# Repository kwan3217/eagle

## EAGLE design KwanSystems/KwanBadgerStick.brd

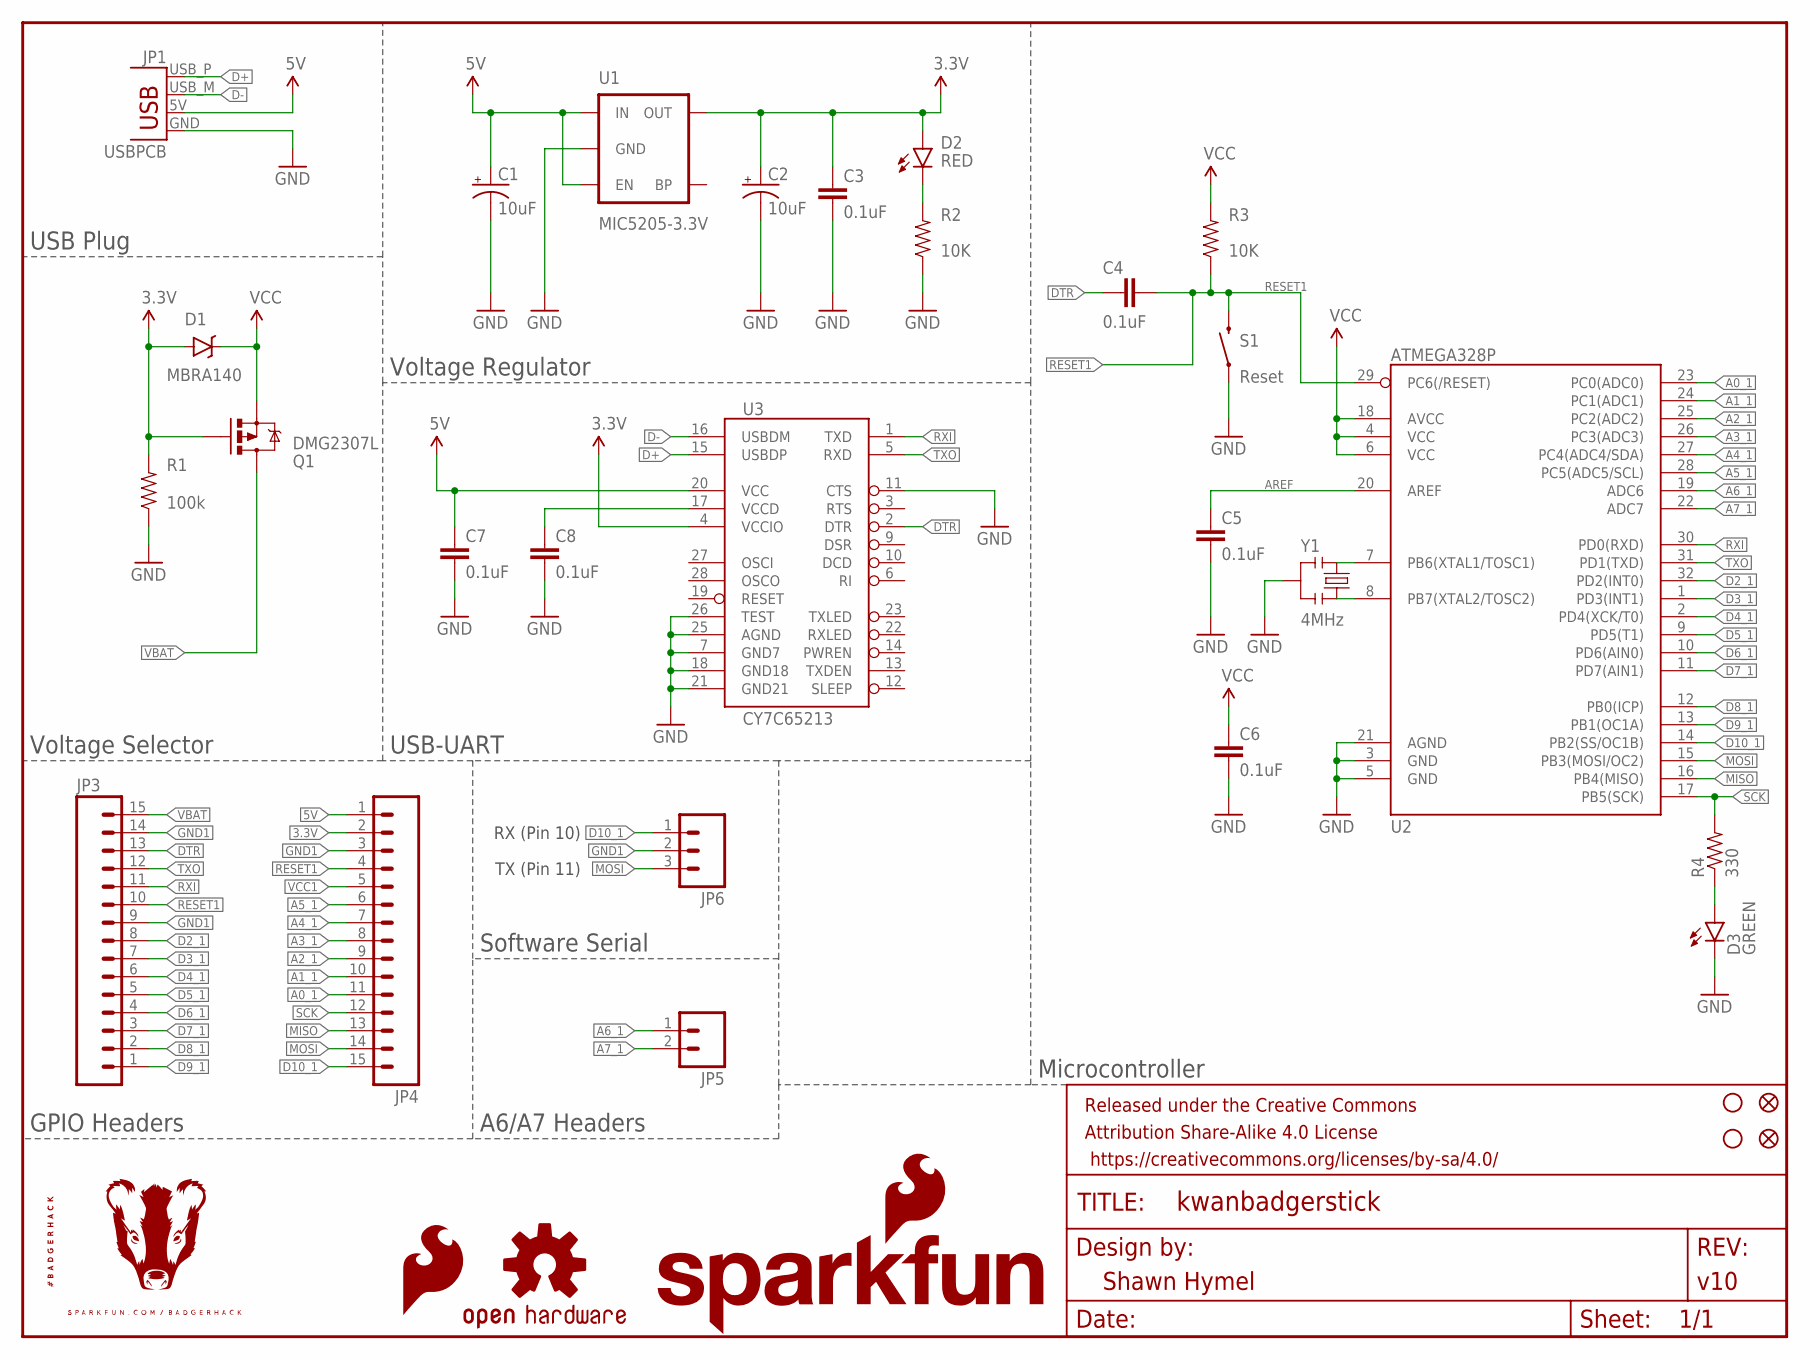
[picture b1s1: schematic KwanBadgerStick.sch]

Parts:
C1, C2: 10uF; EIA3216
C3, C4, C5, C6, C7, C8: 0.1uF; 0603-CAP
D1: MBRA140; SMA-DIODE
D2: RED; LED-0603
D3: GREEN; LED-0603
FID1, FID2: FIDUCIAL1X2; FIDUCIAL-1X2
FRAME1: FRAME-LETTER; CREATIVE_COMMONS
JP1: USBPCB; USB-A-PCB
JP3, JP4: M15LOCK_NO_SILK; 1X15_LOCK_NO_SILK
JP5: M021X02_NO_SILK; 1X02_NO_SILK
JP6: M03LOCK Female; 1X03_LOCK_NO_SILK
LOGO1: SFE_LOGO_FLAME.1_INCH; SFE_LOGO_FLAME_.1
LOGO2: OSHW-LOGOS; OSHW-LOGO-S
Q1: DMG2307L; SOT23-3
R1: 100k; 0603-RES
R2, R3: 10K; 0603-RES
R4: 330; 0603-RES
S1: SWITCH-MOMENTARY-2SMD-REDUNDANT; TACTILE-SWITCH-SMD
STANDOFF1, STANDOFF2: STAND-OFF
U1: MIC5205-3.3V; SOT23-5
U2: ATMEGA328P; TQFP32-08
U3: CY7C65213; SSOP28DB
U$1: SFE_LOGO_NAME_FLAME.1_INCH; SFE_LOGO_NAME_FLAME_.1
U$2: BADGERHACK_LOGODUMMY; DUMMY
Y1: 4MHz; RESONATOR-SMD_MED

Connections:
3.3V: C2.A (+), C3.1, D1.A, D2.A, JP4.2, Q1.1 (G), R1.2, U1.5 (OUT), U3.4 (VCCIO)
5V: C1.A (+), C7.1, JP1.5V (VBUS), JP4.1, U1.1 (IN), U1.3 (EN), U3.20 (VCC)
A0_1: JP4.11, U2.23 (PC0(ADC0))
A1_1: JP4.10, U2.24 (PC1(ADC1))
A2_1: JP4.9, U2.25 (PC2(ADC2))
A3_1: JP4.8, U2.26 (PC3(ADC3))
A4_1: JP4.7, U2.27 (PC4(ADC4/SDA))
A5_1: JP4.6, U2.28 (PC5(ADC5/SCL))
A6_1: JP5.1, U2.19 (ADC6)
A7_1: JP5.2, U2.22 (ADC7)
AREF: C5.1, U2.20 (AREF)
D2_1: JP3.8, U2.32 (PD2(INT0))
D3_1: JP3.7, U2.1 (PD3(INT1))
D4_1: JP3.6, U2.2 (PD4(XCK/T0))
D5_1: JP3.5, U2.9 (PD5(T1))
D6_1: JP3.4, U2.10 (PD6(AIN0))
D7_1: JP3.3, U2.11 (PD7(AIN1))
D8_1: JP3.2, U2.12 (PB0(ICP))
D9_1: JP3.1, U2.13 (PB1(OC1A))
D10_1: JP4.15, JP6.1, U2.14 (PB2(SS/OC1B))
D+: JP1.USB_P (D+), U3.15 (USBDP)
D-: JP1.USB_M (D-), U3.16 (USBDM)
DTR: C4.1, JP3.13, U3.2 (DTR)
GND1: C1.C (-), C2.C (-), C3.2, C5.2, C6.2, C7.2, C8.2, D3.C, JP1.GND, JP3.9, JP3.14, JP4.3, JP6.2, R1.1, R2.1, S1.1, S1.2 (1), U1.2 (GND), U2.3 (GND), U2.5 (GND), U2.21 (AGND), U3.7 (GND7), U3.11 (CTS), U3.18 (GND18), U3.21 (GND21), U3.25 (AGND), U3.26 (TEST), Y1.2
MISO: JP4.13, U2.16 (PB4(MISO))
MOSI: JP4.14, JP6.3, U2.15 (PB3(MOSI/OC2))
unnamed: D3.A, R4.1
unnamed: C8.1, U3.17 (VCCD)
unnamed: D2.C, R2.2
unnamed: U2.7 (PB6(XTAL1/TOSC1)), Y1.1
unnamed: U2.8 (PB7(XTAL2/TOSC2)), Y1.3
RESET1: C4.2, JP3.10, JP4.4, R3.1, S1.3 (2), S1.4 (2), U2.29 (PC6(/RESET))
RXI: JP3.11, U2.30 (PD0(RXD)), U3.1 (TXD)
SCK: JP4.12, R4.2, U2.17 (PB5(SCK))
TXO: JP3.12, U2.31 (PD1(TXD)), U3.5 (RXD)
VBAT: JP3.15, Q1.3 (D)
VCC1: C6.1, D1.C, JP4.5, Q1.2 (S), R3.2, U2.4 (VCC), U2.6 (VCC), U2.18 (AVCC)

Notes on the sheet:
RX (Pin 10)
TX (Pin 11)
USB Plug
Voltage Selector
GPIO Headers
A6/A7 Headers
Software Serial
USB-UART
Voltage Regulator
Microcontroller

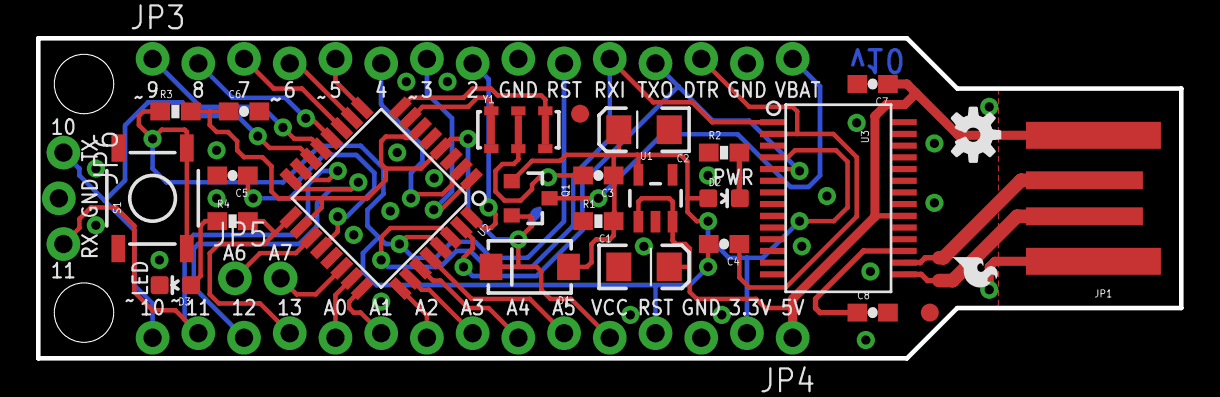
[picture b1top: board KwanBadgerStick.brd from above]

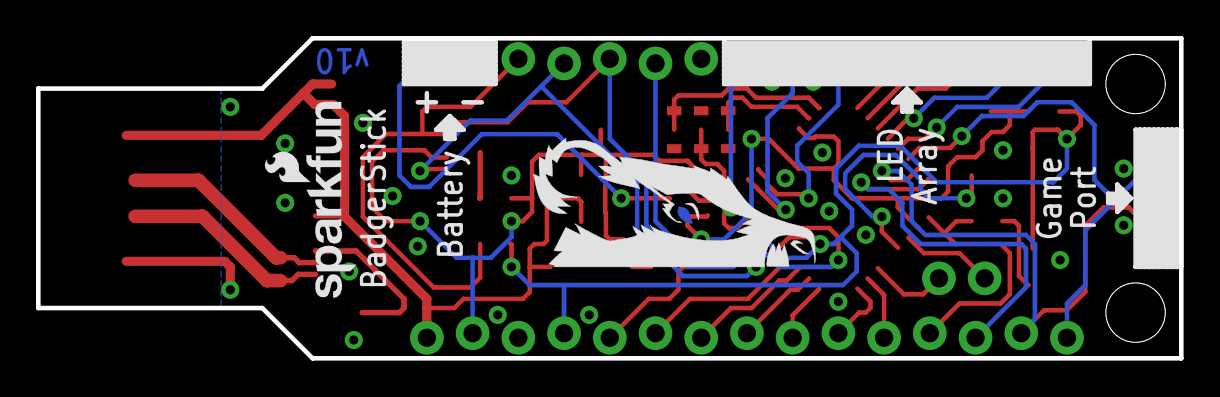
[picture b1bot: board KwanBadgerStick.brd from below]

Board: 2 copper layers, 63.5 x 17.8 mm, 36 parts (2 on the bottom side), 37 nets.

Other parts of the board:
U$3: HALF_BADGER

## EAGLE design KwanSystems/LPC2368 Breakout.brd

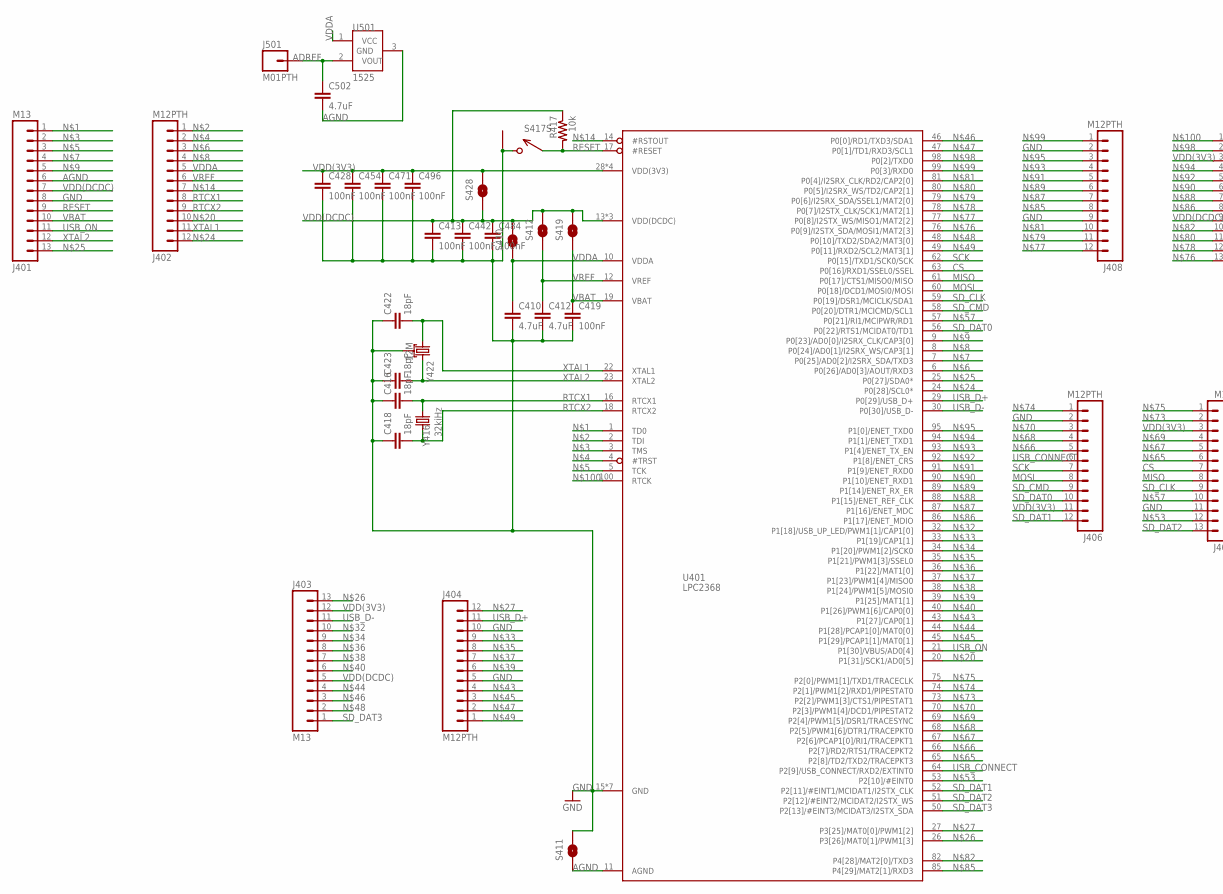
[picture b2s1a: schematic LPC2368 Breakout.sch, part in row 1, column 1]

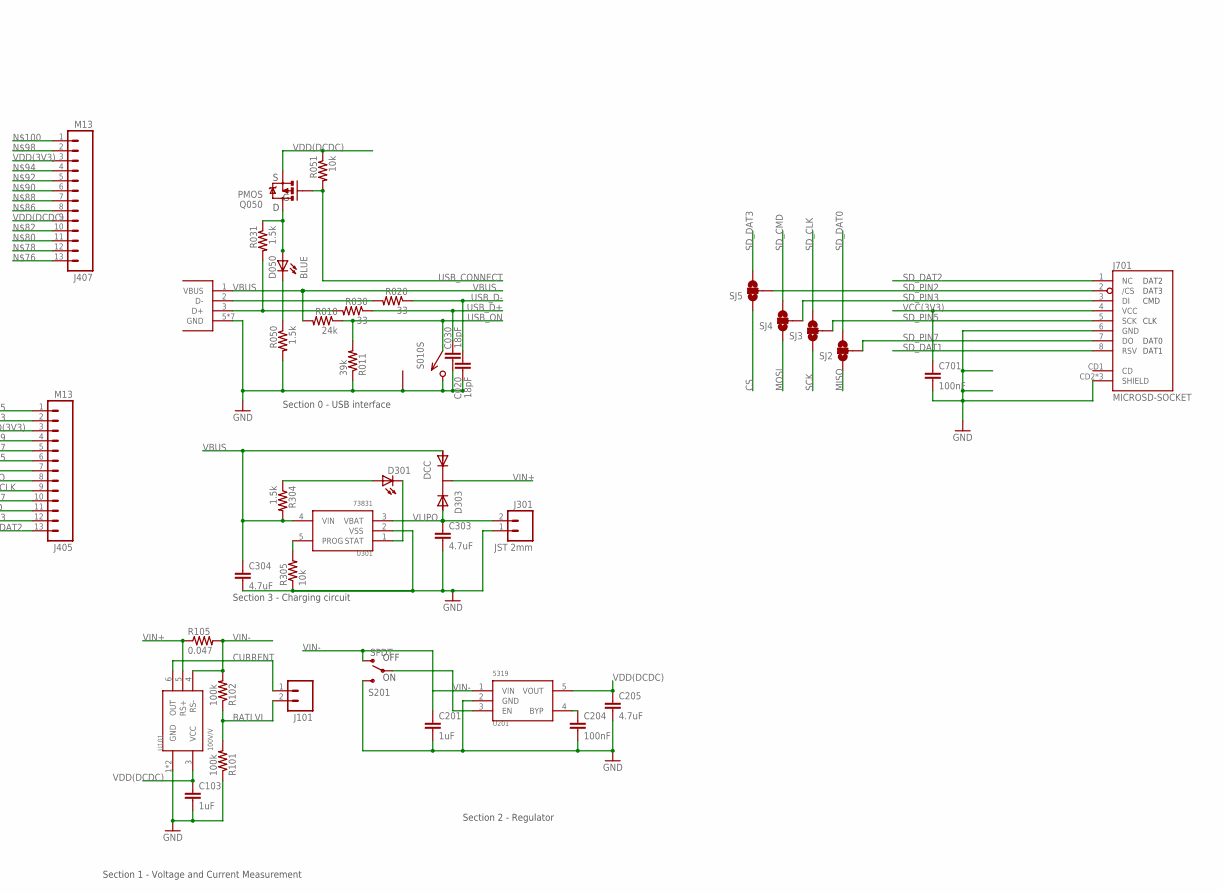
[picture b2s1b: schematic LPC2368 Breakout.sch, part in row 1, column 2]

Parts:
C020, C030, C416, C418, C422, C423: 18pF; 0402-CAP
C103, C201: 1uF; 0402-CAP
C204, C413, C419, C428, C442, C454, C471, C484, C496, C701: 100nF; 0402-CAP
C205, C303, C304, C410, C412, C502: 4.7uF; 0402-CAP
D050: BLUE; LED-0603
D301: YELLOW; LED-0603
D303: DCC; SOT-23-3
J001: USB_MICROB_JST; UB-MC5BR3-SD204-4S
J101: M02PTH; 1X02
J301: JST 2mm; JST-2-SMD
J401, J403, J405, J407: M13; 1X13
J402, J404, J406, J408: M12PTH; 1X12
J501: M01PTH; 1X01
J701: MICROSD-SOCKET; MICROSD-SOCKET-PP
Q050: PMOS; SOT23-3
R010: 24k; 0402-RES
R011: 39k; 0402-RES
R020, R030: 33; 0402-RES
R031, R050, R304: 1.5k; 0402-RES
R051, R305, R417: 10k; 0402-RES
R101, R102: 100k; 0402-RES
R105: 0.047; 0402-RES
S010, S417: SPST; B3U-1100P
S201: SPDT; AYZ0202
S410, S411, S412, S419, S428: SOLDERJUMPERNO; SJ_2S-NO
SJ2, SJ3, SJ4, SJ5: SOLDERJUMPER_2WAYS; SJ_3
U101: 100V/V; SOT-23-6
U201: 5319; SOT-23-5
U301: 73831; SOT-23-5
U401: LPC2368; LQFP100
U501: 1525; SOT-23-3
Y416: 32kiHz; CRYSTAL-32KHZ-SMD
Y422: 12M; CRYSTAL_SMD

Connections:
ADREF: C502.1, J501.1, U501.2 (VOUT)
AGND: C502.2, J401.6, S411.1, U401.11 (AGND), U501.3 (GND)
BATLVL: J101.2, R101.2, R102.1
CONN_D+: J001.3 (D+), R030.2, R031.2
CONN_D-: J001.2 (D-), R020.2
CS: J405.7, SJ5.1, U401.63 (P0[16]/RXD1/SSEL0/SSEL)
CURRENT: J101.1, U101.6 (OUT)
C_STAT: D301.C, U301.1 (STAT)
DR_STAT: D301.A, R304.1
MISO: J405.8, SJ2.1, U401.61 (P0[17]/CTS1/MISO0/MISO)
MOSI: J406.8, SJ4.1, U401.60 (P0[18]/DCD1/MOSI0/MOSI)
unnamed: J401.1, U401.1 (TD0)
unnamed: J402.1, U401.2 (TDI)
unnamed: J401.2, U401.3 (TMS)
unnamed: J402.2, U401.4 (#TRST)
unnamed: J401.3, U401.5 (TCK)
unnamed: J402.3, U401.6 (P0[26]/AD0[3]/AOUT/RXD3)
unnamed: J401.4, U401.7 (P0[25]/AD0[2]/I2SRX_SDA/TXD3)
unnamed: J402.4, U401.8 (P0[24]/AD0[1]/I2SRX_WS/CAP3[1])
unnamed: J401.5, U401.9 (P0[23]/AD0[0]/I2SRX_CLK/CAP3[0])
unnamed: R305.2, U301.5 (PROG)
unnamed: J402.7, U401.14 (#RSTOUT)
unnamed: C204.1, U201.4 (BYP)
unnamed: D050.C, R050.1
unnamed: S201.2, U201.3 (EN)
unnamed: J402.10, U401.20 (P1[31]/SCK1/AD0[5])
unnamed: J402.12, U401.24 (P0[28]/SCL0*)
unnamed: J401.13, U401.25 (P0[27]/SDA0*)
unnamed: J403.13, U401.26 (P3[26]/MAT0[1]/PWM1[3])
unnamed: J404.12, U401.27 (P3[25]/MAT0[0]/PWM1[2])
unnamed: D050.A, Q050.3 (D), R031.1
unnamed: J403.10, U401.32 (P1[18]/USB_UP_LED/PWM1[1]/CAP1[0])
unnamed: J404.9, U401.33 (P1[19]/CAP1[1])
unnamed: J403.9, U401.34 (P1[20]/PWM1[2]/SCK0)
unnamed: J404.8, U401.35 (P1[21]/PWM1[3]/SSEL0)
unnamed: J403.8, U401.36 (P1[22]/MAT1[0])
unnamed: J404.7, U401.37 (P1[23]/PWM1[4]/MISO0)
unnamed: J403.7, U401.38 (P1[24]/PWM1[5]/MOSI0)
unnamed: J404.6, U401.39 (P1[25]/MAT1[1])
unnamed: J403.6, U401.40 (P1[26]/PWM1[6]/CAP0[0])
unnamed: J404.4, U401.43 (P1[27]/CAP0[1])
unnamed: J403.4, U401.44 (P1[28]/PCAP1[0]/MAT0[0])
unnamed: J404.3, U401.45 (P1[29]/PCAP1[1]/MAT0[1])
unnamed: J403.3, U401.46 (P0[0]/RD1/TXD3/SDA1)
unnamed: J404.2, U401.47 (P0[1]/TD1/RXD3/SCL1)
unnamed: J403.2, U401.48 (P0[10]/TXD2/SDA2/MAT3[0])
unnamed: J404.1, U401.49 (P0[11]/RXD2/SCL2/MAT3[1])
unnamed: J405.12, U401.53 (P2[10]/#EINT0)
unnamed: J405.10, U401.57 (P0[21]/RI1/MCIPWR/RD1)
unnamed: J405.6, U401.65 (P2[8]/TD2/TXD2/TRACEPKT3)
unnamed: J406.5, U401.66 (P2[7]/RD2/RTS1/TRACEPKT2)
unnamed: J405.5, U401.67 (P2[6]/PCAP1[0]/RI1/TRACEPKT1)
unnamed: J406.4, U401.68 (P2[5]/PWM1[6]/DTR1/TRACEPKT0)
unnamed: J405.4, U401.69 (P2[4]/PWM1[5]/DSR1/TRACESYNC)
unnamed: J406.3, U401.70 (P2[3]/PWM1[4]/DCD1/PIPESTAT2)
unnamed: J405.2, U401.73 (P2[2]/PWM1[3]/CTS1/PIPESTAT1)
unnamed: J406.1, U401.74 (P2[1]/PWM1[2]/RXD1/PIPESTAT0)
unnamed: J405.1, U401.75 (P2[0]/PWM1[1]/TXD1/TRACECLK)
unnamed: J407.13, U401.76 (P0[9]/I2STX_SDA/MOSI1/MAT2[3])
unnamed: J408.12, U401.77 (P0[8]/I2STX_WS/MISO1/MAT2[2])
unnamed: J407.12, U401.78 (P0[7]/I2STX_CLK/SCK1/MAT2[1])
unnamed: J408.11, U401.79 (P0[6]/I2SRX_SDA/SSEL1/MAT2[0])
unnamed: J407.11, U401.80 (P0[5]/I2SRX_WS/TD2/CAP2[1])
unnamed: J408.10, U401.81 (P0[4]/I2SRX_CLK/RD2/CAP2[0])
unnamed: J407.10, U401.82 (P4[28]/MAT2[0]/TXD3)
unnamed: J408.8, U401.85 (P4[29]/MAT2[1]/RXD3)
unnamed: J407.8, U401.86 (P1[17]/ENET_MDIO)
unnamed: J408.7, U401.87 (P1[16]/ENET_MDC)
unnamed: J407.7, U401.88 (P1[15]/ENET_REF_CLK)
unnamed: J408.6, U401.89 (P1[14]/ENET_RX_ER)
unnamed: J407.6, U401.90 (P1[10]/ENET_RXD1)
unnamed: J408.5, U401.91 (P1[9]/ENET_RXD0)
unnamed: J407.5, U401.92 (P1[8]/ENET_CRS)
unnamed: J408.4, U401.93 (P1[4]/ENET_TX_EN)
unnamed: J407.4, U401.94 (P1[1]/ENET_TXD1)
unnamed: J408.3, U401.95 (P1[0]/ENET_TXD0)
unnamed: J407.2, U401.98 (P0[2]/TXD0)
unnamed: J408.1, U401.99 (P0[3]/RXD0)
unnamed: J407.1, U401.100 (RTCK)
RESET: J401.9, R417.2, S417.P$1 (1), U401.17 (#RESET)
RTCX1: C416.2, J402.8, U401.16 (RTCX1), Y416.1, Y416.X1 (1); also elsewhere on the board
RTCX2: C418.2, J402.9, U401.18 (RTCX2), Y416.2, Y416.X2 (2)
SCK: J406.7, SJ3.1, U401.62 (P0[15]/TXD1/SCK0/SCK)
SD_CLK: J405.9, SJ3.3, U401.59 (P0[19]/DSR1/MCICLK/SDA1)
SD_CMD: J406.9, SJ4.3, U401.58 (P0[20]/DTR1/MCICMD/SCL1)
SD_DAT0: J406.10, SJ2.3, U401.56 (P0[22]/RTS1/MCIDAT0/TD1)
SD_DAT1: J406.12, J701.8 (RSV), U401.52 (P2[11]/#EINT1/MCIDAT1/I2STX_CLK)
SD_DAT2: J405.13, J701.1 (NC), U401.51 (P2[12]/#EINT2/MCIDAT2/I2STX_WS)
SD_DAT3: J403.1, SJ5.3, U401.50 (P2[13]/#EINT3/MCIDAT3/I2STX_SDA)
SD_PIN2: J701.2 (/CS), SJ5.2
SD_PIN3: J701.3 (DI), SJ4.2
SD_PIN5: J701.5 (SCK), SJ3.2
SD_PIN7: J701.7 (DO), SJ2.2
USB_CONNECT: J406.6, Q050.1 (G), R051.2, U401.64 (P2[9]/USB_CONNECT/RXD2/EXTINT0)
USB_D+: C030.1, J404.11, R030.1, U401.29 (P0[29]/USB_D+)
USB_D-: C020.1, J403.11, R020.1, U401.30 (P0[30]/USB_D-)
USB_ON: J401.11, R010.1, R011.2, S010.P$1 (1), U401.21 (P1[30]/VBUS/AD0[4])
VBAT: C419.1, J401.10, S419.1, U401.19 (VBAT)
VBUS: C304.1, D303.1 (A1), J001.1 (VBUS), R010.2, R304.2, U301.4 (VIN)
VCC(3V3): C701.1, J701.4 (VCC)
VDD(3V3): C428.1, C454.1, C471.1, C496.1, J403.12, J405.3, J406.11, J407.3, S428.2, U401.28 (VDD(3V3)), U401.54 (VDD(3V3)), U401.71 (VDD(3V3)), U401.96 (VDD(3V3))
VDD(DCDC): C103.1, C205.1, C413.1, C442.1, C484.1, J401.7, J403.5, J407.9, Q050.2 (S), R051.1, R417.1, S410.2, S412.2, S419.2, S428.1, U101.3 (VCC), U201.5 (VOUT), U401.13 (VDD(DCDC)), U401.42 (VDD(DCDC)), U401.84 (VDD(DCDC))
VDDA: C410.1, J402.5, S410.1, U401.10 (VDDA), U501.1 (VCC)
VIN+: D303.3 (K), R105.1, U101.5 (RS+)
VLIPO: C303.1, D303.2 (A2), J301.2, U301.3 (VBAT)
VREF: C412.1, J402.6, S412.1, U401.12 (VREF)
XTAL1: C422.2, J402.11, U401.22 (XTAL1), Y422.1
XTAL2: C423.2, J401.12, U401.23 (XTAL2), Y422.3 (2)

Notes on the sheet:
Section 2 - Regulator
Section 3 - Charging circuit
Section 0 - USB interface
Section 1 - Voltage and Current Measurement
OFF

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
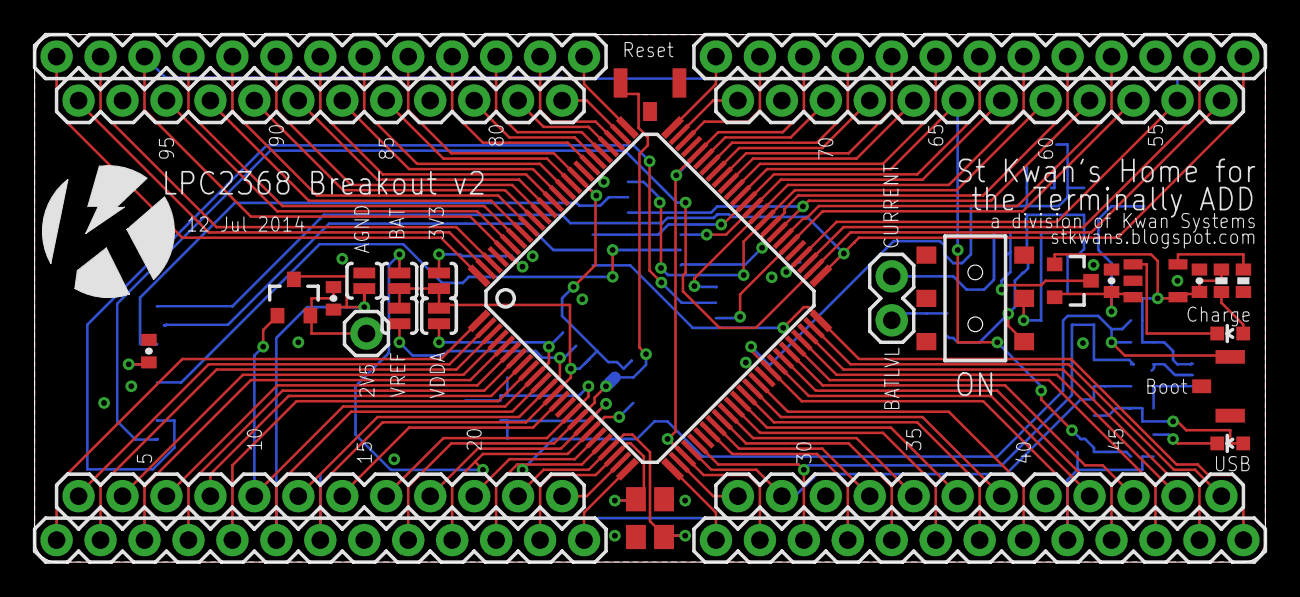
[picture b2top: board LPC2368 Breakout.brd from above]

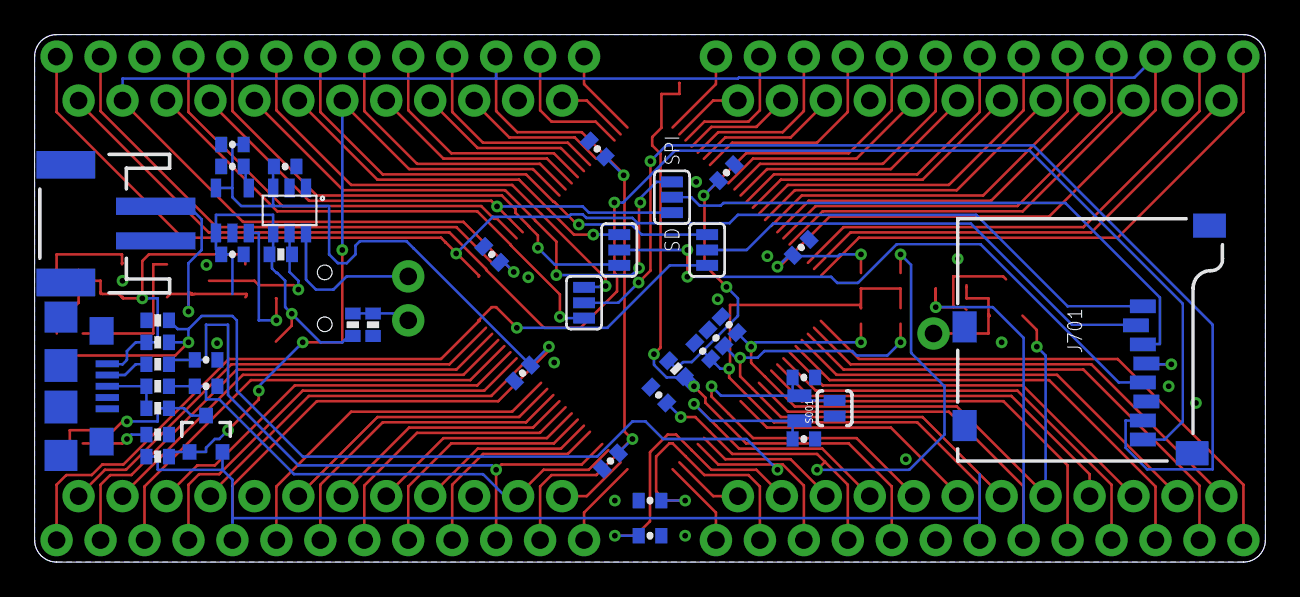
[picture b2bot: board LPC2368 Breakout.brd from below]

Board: 2 copper layers, 71.1 x 30.5 mm, 75 parts (43 on the bottom side), 110 nets.

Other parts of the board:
S001: SOLDERJUMPERNO; SJ_2S-NO
U$1: KWAN_CIRCLE

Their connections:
RTCX1: S001.2; also elsewhere on the board

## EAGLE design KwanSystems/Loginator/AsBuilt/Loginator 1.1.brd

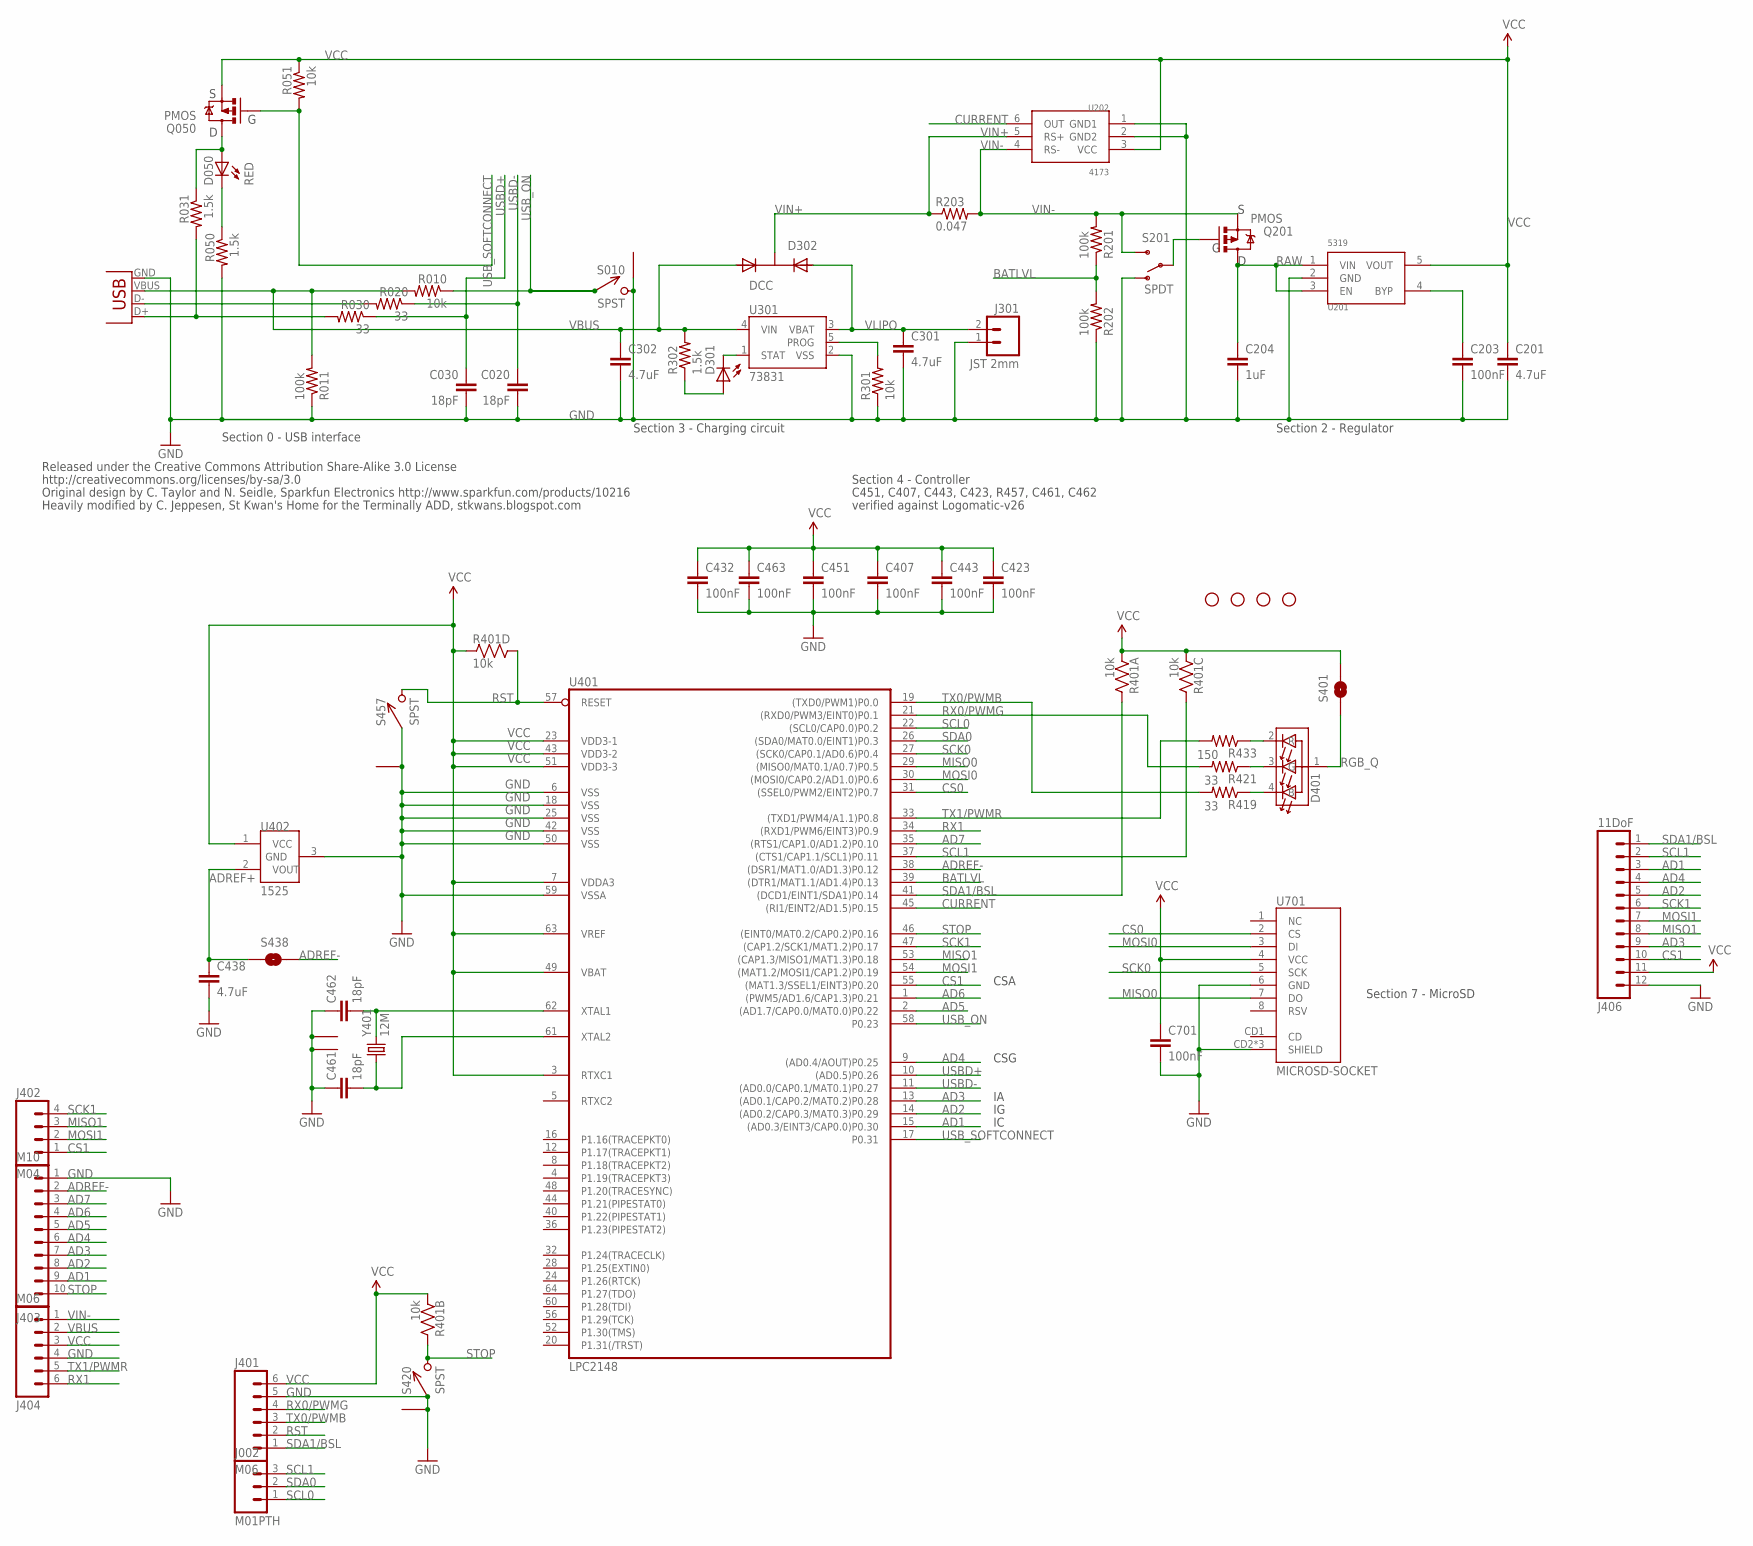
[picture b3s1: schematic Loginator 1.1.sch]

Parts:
C020, C030, C461, C462: 18pF; 0402-CAP
C201, C301, C302, C438: 4.7uF; 0402-CAP
C203, C407, C423, C432, C443, C451, C463, C701: 100nF; 0402-CAP
C204: 1uF; 0402-CAP
D050, D301: RED; LED-0603
D302: DCC; SOT-23-3
D401: HSMF-C118
J001: USBSMD; USB-MINIB
J002: M01PTH; 1X03
J301: JST 2mm; JST-2-SMD
J401, J404: M06; 1X06
J402: M04; 1X04
J403: M10; 1X10
J406: 11DoF; 1X12
JP1, JP2, JP3, JP4: STAND-OFF
Q050, Q201: PMOS; SOT23-3
R010, R051, R301: 10k; 0402-RES
R011, R201, R202: 100k; 0402-RES
R020, R030, R419, R421: 33; 0402-RES
R031, R050, R302: 1.5k; 0402-RES
R203: 0.047; 0402-RES
R401: 10k; CRA04
R433: 150; 0402-RES
S010, S420, S457: SPST; B3U-1100P
S201: SPDT; AYZ0202
S401, S438: SOLDERJUMPERNO; SJ_2S-NO
U201: 5319; SOT-23-5
U202: 4173; SOT-23-6
U301: 73831; SOT23-5
U401: LPC2148; SQFP-S-10X10-64
U402: 1525; SOT-23-3
U701: MICROSD-SOCKET; MICROSD-SOCKET-PP
Y401: 12M; CRYSTAL_SMD

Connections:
AD1: J403.9, J406.3, U401.15 ((AD0.3/EINT3/CAP0.0)P0.30)
AD2: J403.8, J406.5, U401.14 ((AD0.2/CAP0.3/MAT0.3)P0.29)
AD3: J403.7, J406.9, U401.13 ((AD0.1/CAP0.2/MAT0.2)P0.28)
AD4: J403.6, J406.4, U401.9 ((AD0.4/AOUT)P0.25)
AD5: J403.5, U401.2 ((AD1.7/CAP0.0/MAT0.0)P0.22)
AD6: J403.4, U401.1 ((PWM5/AD1.6/CAP1.3)P0.21)
AD7: J403.3, U401.35 ((RTS1/CAP1.0/AD1.2)P0.10)
ADREF+: C438.1, S438.1, U402.2 (VOUT)
ADREF-: J403.2, S438.2, U401.38 ((DSR1/MAT1.0/AD1.3)P0.12)
BATLVL: R201.1, R202.2, U401.39 ((DTR1/MAT1.1/AD1.4)P0.13)
CONN_D+: J001.D+, R030.2, R031.2
CONN_D-: J001.D-, R020.2
CS0: U401.31 ((SSEL0/PWM2/EINT2)P0.7), U701.2 (CS)
CS1: J402.1, J406.10, U401.55 ((MAT1.3/SSEL1/EINT3)P0.20)
CURRENT: U202.6 (OUT), U401.45 ((RI1/EINT2/AD1.5)P0.15)
DB: D401.4 (B), R419.1
DG: D401.3 (G), R421.1
DR: D401.2 (R), R433.1
GND: C020.2, C030.2, C201.2, C203.2, C204.2, C301.2, C302.2, C407.2, C423.2, C432.2, C438.2, C443.2, C451.2, C461.1, C462.1, C463.2, C701.2, J001.GND, J301.1, J401.5, J403.1, J404.4, J406.12, R011.1, R050.2, R202.1, R301.1, S010.P$2 (2), S010.P$3 (1), S201.1 (O), S420.P$1 (1), S420.P$3 (1), S457.P$1 (1), S457.P$3 (1), U201.2 (GND), U202.1 (GND1), U202.2 (GND2), U301.2 (VSS), U401.6 (VSS), U401.18 (VSS), U401.25 (VSS), U401.42 (VSS), U401.50 (VSS), U401.59 (VSSA), U402.3 (GND), U701.6 (GND), U701.CD2 (SHIELD), U701.GND1 (SHIELD), U701.GND3 (SHIELD), Y401.2 (1), Y401.4 (1)
MISO0: U401.29 ((MISO0/MAT0.1/A0.7)P0.5), U701.7 (DO)
MISO1: J402.3, J406.8, U401.53 ((CAP1.3/MISO1/MAT1.3)P0.18)
MOSI0: U401.30 ((MOSI0/CAP0.2/AD1.0)P0.6), U701.3 (DI)
MOSI1: J402.2, J406.7, U401.54 ((MAT1.2/MOSI1/CAP1.2)P0.19)
unnamed: D301.A, R302.1
unnamed: R301.2, U301.5 (PROG)
unnamed: D301.C, U301.1 (STAT)
unnamed: D050.A, Q050.3 (D), R031.1
unnamed: D050.C, R050.1
unnamed: Q201.1 (G), S201.2
unnamed: C203.1, U201.4 (BYP)
RAW: C204.1, Q201.3 (D), U201.1 (VIN), U201.3 (EN)
RGB_Q: D401.1 (A), S401.1
RST: J401.2, R401.5 (2), S457.P$2 (2), U401.57 (RESET)
RX0/PWMG: J401.4, R421.2, U401.21 ((RXD0/PWM3/EINT0)P0.1)
RX1: J404.6, U401.34 ((RXD1/PWM6/EINT3)P0.9)
SCK0: U401.27 ((SCK0/CAP0.1/AD0.6)P0.4), U701.5 (SCK)
SCK1: J402.4, J406.6, U401.47 ((CAP1.2/SCK1/MAT1.2)P0.17)
SCL0: J002.1, U401.22 ((SCL0/CAP0.0)P0.2)
SCL1: J002.3, J406.2, R401.6 (2), U401.37 ((CTS1/CAP1.1/SCL1)P0.11)
SDA0: J002.2, U401.26 ((SDA0/MAT0.0/EINT1)P0.3)
SDA1/BSL: J401.1, J406.1, R401.8 (2), U401.41 ((DCD1/EINT1/SDA1)P0.14)
STOP: J403.10, R401.7 (2), S420.P$2 (2), U401.46 ((EINT0/MAT0.2/CAP0.2)P0.16)
TX0/PWMB: J401.3, R419.2, U401.19 ((TXD0/PWM1)P0.0)
TX1/PWMR: J404.5, R433.2, U401.33 ((TXD1/PWM4/A1.1)P0.8)
USBD+: C030.1, R030.1, U401.10 ((AD0.5)P0.26)
USBD-: C020.1, R020.1, U401.11 ((AD0.0/CAP0.1/MAT0.1)P0.27)
USB_ON: R010.1, S010.P$1 (1), U401.58 (P0.23)
USB_SOFTCONNECT: Q050.1 (G), R051.2, U401.17 (P0.31)
VBUS: C302.1, D302.1 (A1), J001.VBUS, J404.2, R010.2, R011.2, R302.2, U301.4 (VIN)
VCC: C201.1, C407.1, C423.1, C432.1, C443.1, C451.1, C463.1, C701.1, J401.6, J404.3, J406.11, Q050.2 (S), R051.1, R401.1, R401.2 (1), R401.3 (1), R401.4 (1), S401.2, U201.5 (VOUT), U202.3 (VCC), U401.3 (RTXC1), U401.7 (VDDA3), U401.23 (VDD3-1), U401.43 (VDD3-2), U401.49 (VBAT), U401.51 (VDD3-3), U401.63 (VREF), U402.1 (VCC), U701.4 (VCC)
VIN+: D302.3 (K), R203.1, U202.5 (RS+)
VIN-: J404.1, Q201.2 (S), R201.2, R203.2, S201.3 (S), U202.4 (RS-)
VLIPO: C301.1, D302.2 (A2), J301.2, U301.3 (VBAT)
XTAL1: C462.2, U401.62 (XTAL1), Y401.3 (2)
XTAL2: C461.2, U401.61 (XTAL2), Y401.1

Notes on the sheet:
Section 4 - Controller
Section 7 - MicroSD
C451, C407, C443, C423, R457, C461, C462
verified against Logomatic-v26
Section 2 - Regulator
Section 3 - Charging circuit
Section 0 - USB interface
Released under the Creative Commons Attribution Share-Alike 3.0 License
http://creativecommons.org/licenses/by-sa/3.0
Original design by C. Taylor and N. Seidle, Sparkfun Electronics http://www.sparkfun.com/products/10216
Heavily modified by C. Jeppesen, St Kwan's Home for the Terminally ADD, stkwans.blogspot.com
CSG
CSA

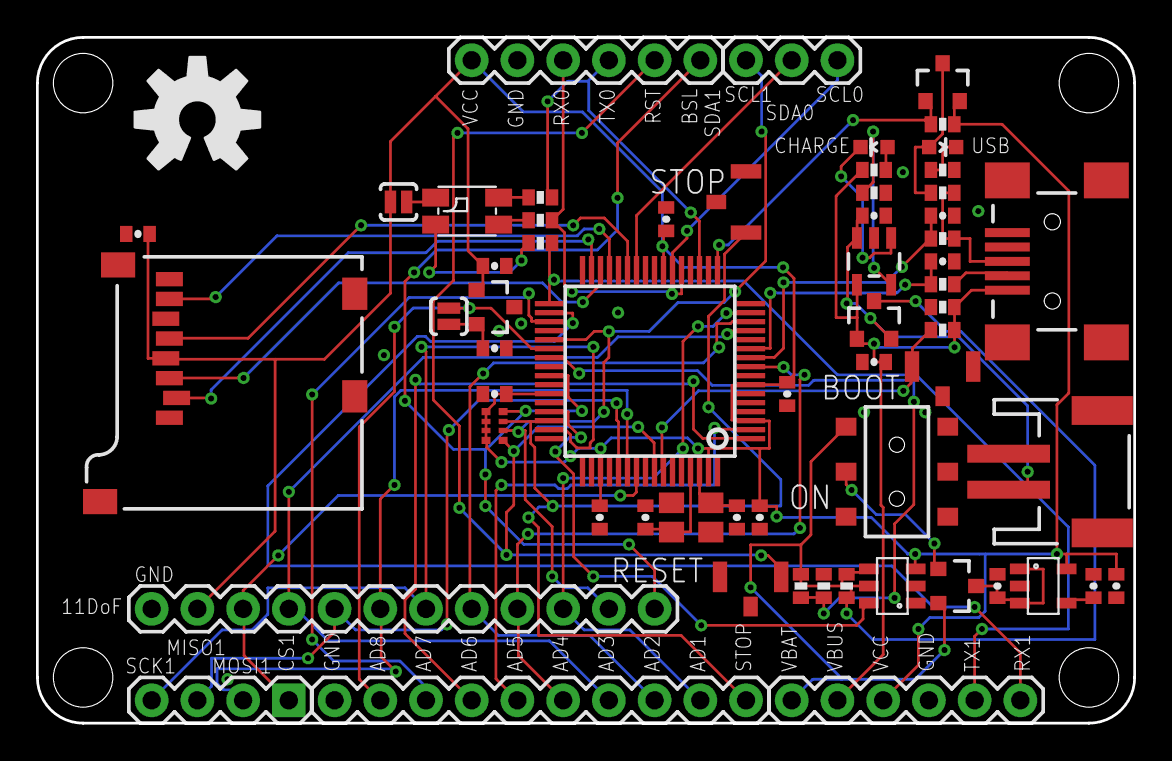
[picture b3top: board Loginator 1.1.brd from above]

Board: 2 copper layers, 61.0 x 38.1 mm, 66 parts (1 on the bottom side), 55 nets.

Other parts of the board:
U$1: KWAN_CIRCLE
U$2: OSHW-LOGO-L

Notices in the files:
parts and their libraries:
SparkFun-Capacitors: Licensing: Creative Commons ShareAlike 4.0 International - https://creativecommons.org/licenses/by-sa/4.0
SparkFun-DiscreteSemi: Licensing: CC v3.0 Share-Alike You are welcome to use this library for commercial purposes.
